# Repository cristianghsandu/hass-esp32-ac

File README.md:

# ESP32 Home Sensor: AC Control #

## General info ##
This is a small board to add Home Assistant control to your old school AC.  
It uses an ESP32 for WiFi connectivity and IR code sending(via the RMT peripheral).  

This is what it looks like when fully built:  

And this is the bare PCB:  

## Building ##
For a Fritzing breadboard schematic see [this Fritzing file](schematic/schematic.fzz).  
For the PCB I used the ESP32 30-pin DoIT devkit board footprint from this [repo](https://github.com/RuiSantosdotme/ESP32-Weather-Shield-PCB).  

The KiCad sources for the PCB are in [this folder](pcb/esp32-ac-board).  

### BOM ###
  
The very few parts you will need are:  

- An ESP32 Doit Devkit v1 (the 30 pin version see [this](https://randomnerdtutorials.com/getting-started-with-esp32/))  
- A NPN transistor in a TO220 package(you could change the design to use a TO92 transistor) like the [2N5296](https://www.mouser.com/ds/2/68/2n5294-46674.pdf)  
- Some male and female pin headers(pitch 2.54'')
- A 12x12mm push button  
- An IR LED
- A DHT22 humidity and temperature sensor  
- A 10k pull up resistor for the DHT22 sensor
- Optional: a 2 pin screw terminal for powering the board externally

### The Code ###

I am using ESP Home to build the firmware [ESP Home](https://esphome.io/).  
The "code" is in this file: [esphome/ac-living.yml](esphome/ac-living.yml).    

### AC Control ###

To control your AC you will need to change the RAW codes in the [config.h](src/config.h) file. I used [AnalysIR](https://www.analysir.com/) to get my raw codes but you could also get them with an Arduinoor even Lirc with irrecord(it's what I initially did). Hardware wise you will either need an Arduino/Raspberry Pi + TSOP4838 receiver(or any other receiver) or maybe an all-in-one solution like the [USB IR Toy](http://dangerousprototypes.com/docs/USB_Infrared_Toy) - which I already had and used.

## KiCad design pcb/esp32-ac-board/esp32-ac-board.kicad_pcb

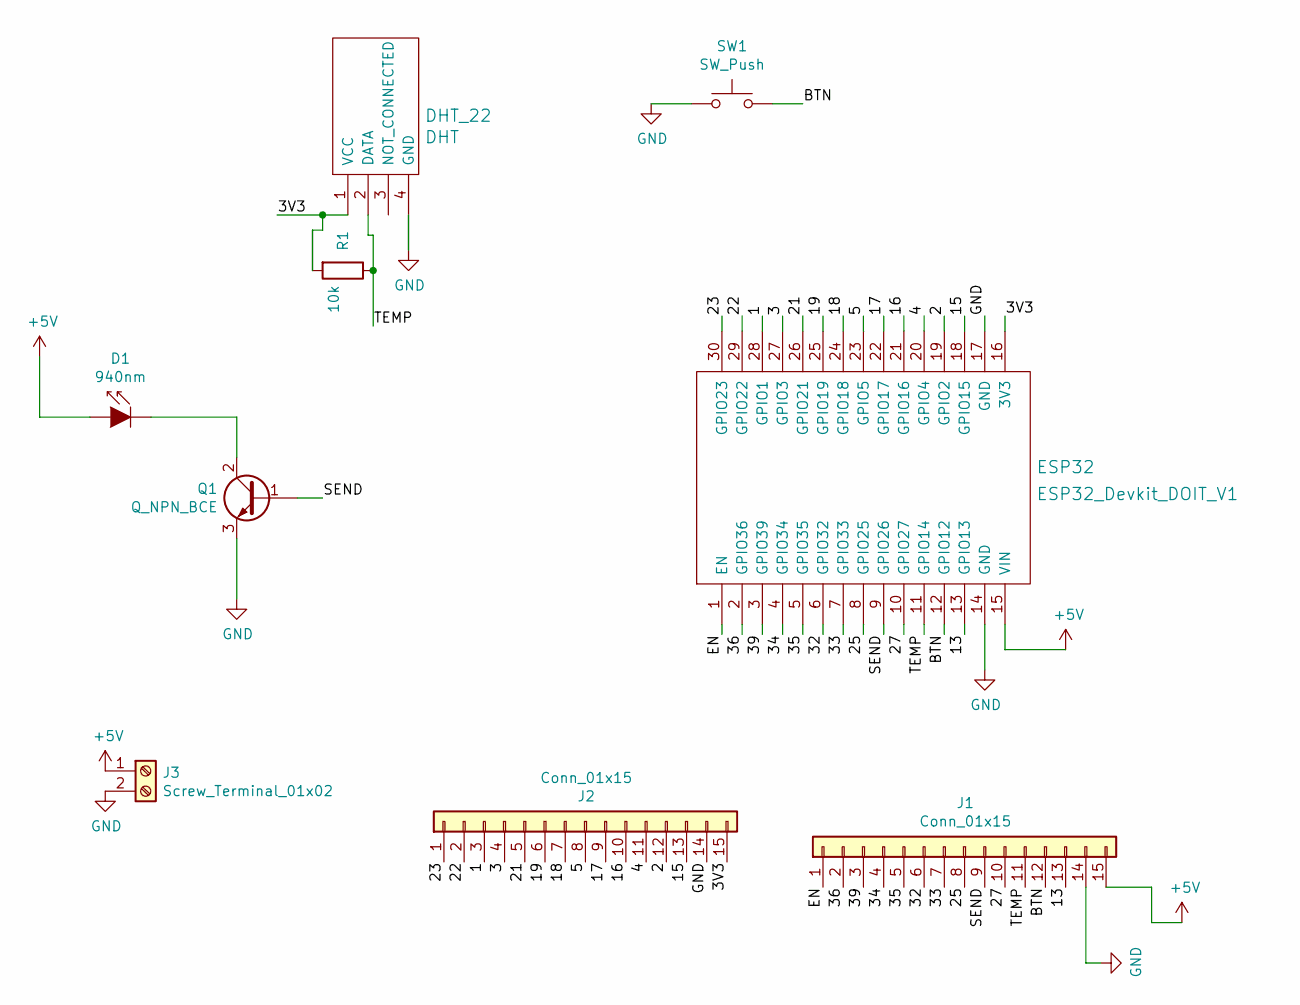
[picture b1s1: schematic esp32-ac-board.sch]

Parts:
D1: 940nm; LED_D5.0mm_IRGrey
DHT_22: DHT
ESP32: ESP32_Devkit_DOIT_V1
J1, J2: Conn_01x15; PinHeader_1x15_P2.54mm_Vertical
J3: Screw_Terminal_01x02; TerminalBlock_bornier-2_P5.08mm
Q1: Q_NPN_BCE; TO-251-3_Vertical
R1: 10k; R_Axial_DIN0204_L3.6mm_D1.6mm_P5.08mm_Horizontal
SW1: SW_Push; SW_PUSH-12mm_Wuerth-430476085716

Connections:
+5V: D1.2 (A), ESP32.15 (VIN), J1.15, J3.1
/1: ESP32.28 (GPIO1), J2.3
/2: ESP32.19 (GPIO2), J2.12
/3: ESP32.27 (GPIO3), J2.4
/3V3: DHT_22.1 (VCC), ESP32.16 (3V3), J2.15, R1.2
/4: ESP32.20 (GPIO4), J2.11
/5: ESP32.23 (GPIO5), J2.8
/13: ESP32.13 (GPIO13), J1.13
/15: ESP32.18 (GPIO15), J2.13
/16: ESP32.21 (GPIO16), J2.10
/17: ESP32.22 (GPIO17), J2.9
/18: ESP32.24 (GPIO18), J2.7
/19: ESP32.25 (GPIO19), J2.6
/21: ESP32.26 (GPIO21), J2.5
/22: ESP32.29 (GPIO22), J2.2
/23: ESP32.30 (GPIO23), J2.1
/25: ESP32.8 (GPIO25), J1.8
/27: ESP32.10 (GPIO27), J1.10
/32: ESP32.6 (GPIO32), J1.6
/33: ESP32.7 (GPIO33), J1.7
/34: ESP32.4 (GPIO34), J1.4
/35: ESP32.5 (GPIO35), J1.5
/36: ESP32.2 (GPIO36), J1.2
/39: ESP32.3 (GPIO39), J1.3
/BTN: ESP32.12 (GPIO12), J1.12, SW1.2
/EN: ESP32.1 (EN), J1.1
/SEND: ESP32.9 (GPIO26), J1.9, Q1.1 (B)
/TEMP: DHT_22.2 (DATA), ESP32.11 (GPIO14), J1.11, R1.1
GND: DHT_22.4 (GND), ESP32.14 (GND), ESP32.17 (GND), J1.14, J2.14, J3.2, Q1.3 (E), SW1.1
unnamed: D1.1 (K), Q1.2 (C)

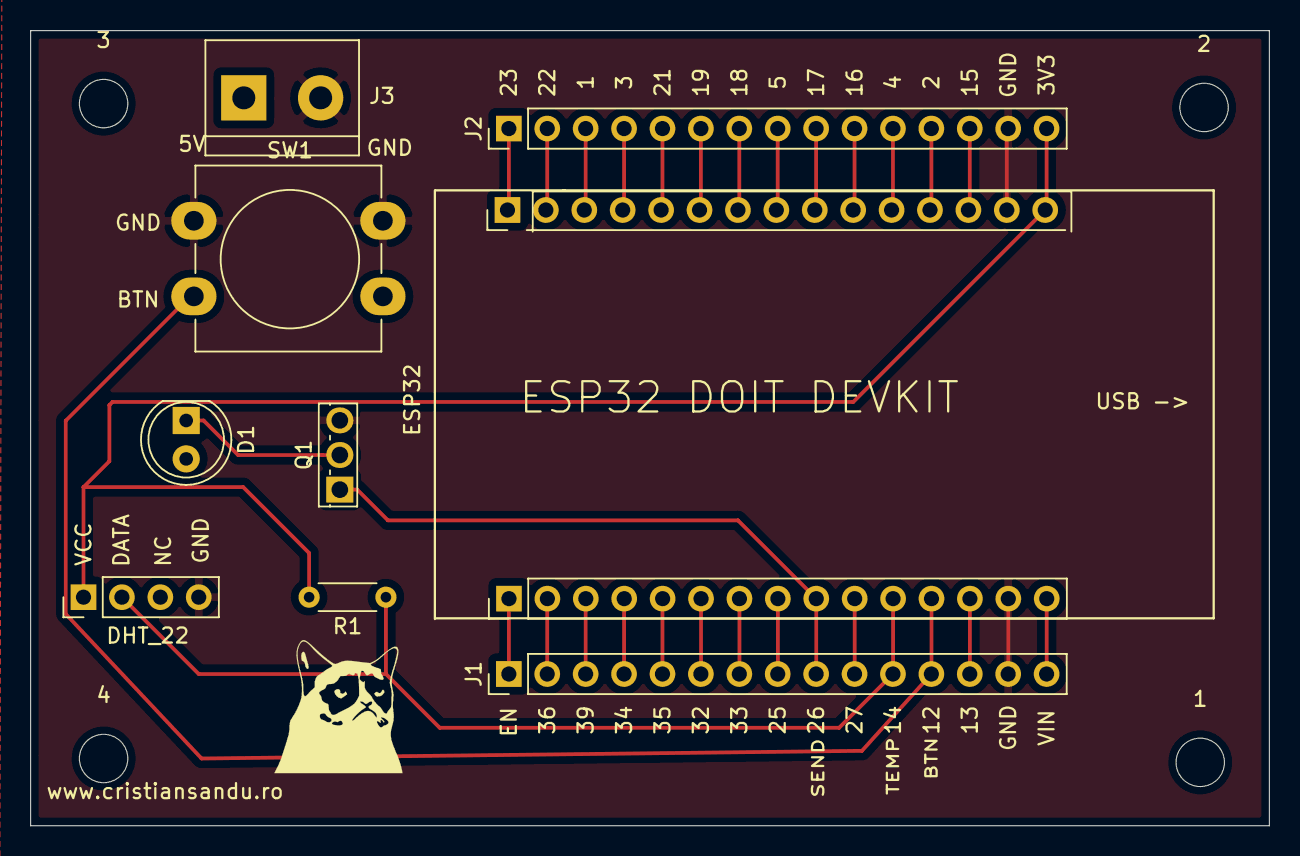
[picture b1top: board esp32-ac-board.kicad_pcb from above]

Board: 2 copper layers, 81.9 x 52.6 mm, 14 parts (1 on the bottom side), 30 nets.

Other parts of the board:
1, 2, 3, 4: MountingHole_3.2mm_M3
LOGO: LOGO; Logo

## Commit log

2018-07-21 add button
2018-07-21 ir led on/off
2018-07-21 short range
2018-07-21 increase power?
2018-07-21 duty 50%
2018-07-21 ac remote
2018-07-21 add ac command
2018-07-22 add mqtt
2018-07-25 differrent duty?
2018-07-25 platformio
2018-07-25 vscode
2018-07-25 RMT example
2018-07-25 add rmt_server example
2018-07-25 zerynth add
2018-07-25 it works on espidf
2018-07-25 minor
2018-07-25 comment
2018-07-26 kill server, split rmt code
2018-07-26 remove more stuff
2018-07-26 switch to Arduino
2018-07-26 convert to arduino code
2018-07-26 clock div?
2018-07-26 fix length
2018-07-26 fix IR code
2018-07-26 unsigned -> signed
2018-07-26 remove zerynth
2018-07-26 remove unused
2018-07-26 add ending
2018-07-26 schematic, initial changes
2018-07-26 mqtt works
2018-07-26 mqtt send ip address
2018-07-26 schematic
2018-07-26 dht22 works
2018-07-26 don;t read all the time
2018-07-27 read less often
2018-07-27 no more settings
2018-07-27 switch to unified DHT lib
2018-07-27 tweak de;ay
2018-07-28 schematic: dht22
2018-07-28 re-arrange
2018-07-28 switch to DHTesp library
2018-07-28 cleaned up a bit code
2018-07-30 ac state
2018-07-30 persist mqtt message
2018-08-08 one button lib
2018-08-16 logic error
2018-08-16 conditional enable
2018-08-16 conditional include
2018-09-19 main.cpp edited online with Bitbucket
2018-10-06 start conversion to home assistant
2018-10-07 checkpoint
2018-10-07 readd esp32_ir_remote
2018-10-07 really add esp32 ir lib
2018-10-07 add sensor
2018-10-07 attempt to override model
2018-10-07 reading works, yey!
2018-10-07 rm whitespace
2018-10-07 don't change names anymore
2018-10-07 push button
2018-10-07 single click works
2018-10-09 add binary state output
2018-10-09 almost fix button
2018-10-09 clicking works
2018-10-09 add second AC switch
2018-10-09 2x click
2018-10-15 new component
2018-10-15 attempt at component on hold
2018-10-15 save
2018-10-15 switch to one button
2018-10-15 remove component
2018-10-15 working prototype
2018-10-15 typo
2018-10-18 humm, not working
2018-10-18 fix ac on/off
2018-10-18 move to config
2018-10-18 move more stuff to config
2018-10-18 move wifi config
2019-05-19 update to newer esphome lib
2019-05-19 update namespace
2019-06-09 PCB design
2019-06-10 add missing lib
2019-06-10 update schematic
2019-06-10 Fix schematic, redo PCB
2019-06-10 update button connection
2019-06-11 Use 5V signal like in https://hackaday.com/2016/11/17/creating-a-pcb-in-everything-kicad-part-1/
2019-06-11 Add traces
2019-06-11 Copper fills
2019-06-11 GERBERs
2019-06-12 Attempt at logo
2019-06-12 logo failure
2019-06-12 fix logo
2019-06-12 add screw terminal for power
2019-06-12 v0.1 sent to JLCPCB.com
2019-06-13 attempt to rotate diode
2019-06-15 circuit experiments
2019-06-15 AC auto
2019-06-15 update triggers
2019-06-15 hope this works
2019-06-15 temp limit
2019-06-27 Fix label
2019-06-28 fix button holes
2019-06-30 add remote automation
2019-07-01 add light switch
2019-07-03 add input_number params
2019-07-03 fix automation
2019-07-06 remove passwords
2019-07-31 ignore wifi config
2019-07-31 remove unused button
2019-07-31 decoded remote codes
2019-08-05 document BOM
2019-08-05 ac details
2019-08-05 another typo
2019-08-05 fix BOM
2019-08-05 10k resistor
2019-08-09 rebuild gerber
2019-08-09 refresh gerber
2019-12-17 change automations
2020-07-03 cleanup platformio stuff
2020-07-03 protect secrets
2020-07-03 reorganize
2020-07-03 protect
2020-07-03 delete
2020-07-03 defaults
2020-07-03 add template
2020-07-03 initial draft, not working
2020-07-03 consolidate ignore
2020-07-03 ir not working
2020-07-03 RMT code works
2020-07-03 on/off by HASS works
2020-07-03 I think it works
2020-07-03 do not start AC on boot
2020-07-03 update entity name
2020-07-06 enable debug
2020-07-06 restore dht22 freq of 60s
2020-07-06 set duty to 30%, huh
2021-07-17 change to 6th sense ac command
2022-05-22 update libs
2024-06-23 updated to latest esphome
2024-07-21 make mqtt optional
2025-06-06 revert to AC 24 code
